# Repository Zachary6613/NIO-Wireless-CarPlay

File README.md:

# NIO Wireless CarPlay

在蔚来车机浏览器中使用的**无线 CarPlay** 方案。树莓派运行车载主机软件
[LIVI](https://github.com/f-io/LIVI)，负责 CarPlay 会话、MFi 认证、蓝牙、Wi-Fi 热点和音视频；
车机无需安装任何 App，只用浏览器打开树莓派提供的网页，即可看到 CarPlay 画面并进行触控操作。

## 工作原理

```text
iPhone
  │  蓝牙：发现、配对、Wi-Fi 切换
  │  Wi-Fi：CarPlay 会话、音视频与控制
  ▼
Raspberry Pi 4/5  +  LIVI
  │  I2C：MFi 证书 / 签名（MFI343S00177 小板）
  │
  │  车内局域网（以太网或第二张 Wi-Fi 网卡）
  ▼
蔚来车机浏览器：网页画面 + 触摸输入（https://<树莓派IP>:8080）
```

- CarPlay 协议与 MFi 认证由 Rust 编写的 **livi-helperd** 守护进程完成
- 画面经局域网推送；HTTP 浏览器使用 MSE 播放 H.264，配置 HTTPS 的浏览器使用 **WebCodecs** 解码并绘制到 canvas
- GStreamer 运行时已随仓库一起提供（linux-x64 / linux-arm64 / macos-arm64），无需自行安装

## 硬件需求

| 项目 | 说明 |
|---|---|
| 树莓派 | 4B 或 5（Pi 3 及更早不满足 OpenGL ES 3.x 要求） |
| 系统 | 64-bit Raspberry Pi OS（Debian 13 Trixie），需桌面环境 |
| MFi 小板 | 本项目 `hardware/` 中的 MFI343S00177 MiniHat，I2C-1，3.3V 常供电 |
| Wi-Fi | 一张独立 5GHz 适配器，作为 CarPlay 热点（勿与车机访问链路混用同一网卡） |
| 蓝牙 | 可先用板载蓝牙验证 |
| 供电 | 稳定的 USB-C 5V 电源 |

> MFi 芯片不是通用空白器件，需要来源合规、已写入有效证书的芯片。本仓库**不包含**任何证书、
> 私钥或认证绕过功能，使用时须遵守 Apple MFi 许可条款。

---

## 从下载到运行（完整步骤）

### 1. 启用 I2C

在树莓派上执行并重启：

```bash
sudo raspi-config nonint do_i2c 0
sudo reboot
```

确认 I2C 总线（标准 40Pin 通常是 bus 1）：

```bash
i2cdetect -l
```

### 2. 下载仓库

```bash
cd ~
git clone https://github.com/Zachary6613/NIO-Wireless-CarPlay.git
cd NIO-Wireless-CarPlay
```

仓库为私有，请确保本机已登录 GitHub（`gh auth login`）或配置好 HTTPS 凭证。

### 3. 安装系统依赖

本仓库自带安装脚本，无需从上游下载。它会安装运行所需的系统依赖（蓝牙、hostapd、
dnsmasq、avahi、pulseaudio、libva 等）以及编译和打包 AppImage 所需的主机工具
（gcc/make 工具链、patchelf、libfuse2、压缩库），但不会下载预编译 AppImage，也不会
改动 I2C 配置：

```bash
./scripts/setup-system.sh
```

> 首次执行 `pnpm run build:linux:arm64` 时，electron-builder 还会自动下载它自己的
> AppImage 工具集（mksquashfs + 静态 runtime），需联网一次；也可用环境变量
> `APPIMAGE_TOOLS_PATH` 指定预先下载好的工具集目录。

脚本结束时会检查 Node.js、pnpm、Rust 工具链。若提示缺失，按以下方式安装：

```bash
# Node.js + pnpm（Raspberry Pi OS / Debian 13 源中的 Node 为 20）
sudo apt-get install -y nodejs npm
sudo corepack enable

# Rust 工具链（编译 livi-helperd 和原生模块）
curl --proto '=https' --tlsv1.2 -sSf https://sh.rustup.rs | sh -s -- -y
. "$HOME/.cargo/env"
```

确认版本：

```bash
node -v        # v20 / v22 / v24
pnpm -v        # 本仓库锁定 pnpm 12.4.1
cargo --version
```

> 注意：不要运行 `software/LIVI/scripts/install/install.sh`。那是上游"预编译 AppImage
> 安装器"，会下载上游 AppImage、创建自启项，并按上游硬件把 MFi 配为软件 I2C bus 2 /
> GPIO 21，与本项目的硬件 I2C-1 / 常供电方案冲突。

### 4. 安装依赖

```bash
cd software/LIVI
pnpm install
```

安装结束后会自动重建原生模块并编译 livi-crypto。

### 5. 编译 helperd 守护进程

CarPlay 连接依赖 livi-helperd：

```bash
pnpm run build:helperd
```

产物位于 `native/livi-helperd/target/release/livi-helperd`。启动脚本会自动找到它；
应用正常运行后也可能把它复制到 `~/.config/LIVI/driver/` 下。

> helperd 通过 `sudo -n -E` 以 root 身份运行（需要访问硬件、管理网络）。请确认当前用户
> 具备免密 sudo，或按需配置 `/etc/sudoers`。

### 6.（可选）生成网页桥接的 HTTPS 证书

WebCodecs 需要安全上下文（HTTPS）。启动脚本检测到下列证书后会默认启用 HTTPS；无证书时才回退到 HTTP/MSE。可生成自签名证书：

```bash
mkdir -p ~/.config/LIVI/web-bridge
openssl req -x509 -newkey rsa:2048 -nodes -days 3650 \
  -keyout ~/.config/LIVI/web-bridge/key.pem \
  -out ~/.config/LIVI/web-bridge/cert.pem \
  -subj "/CN=LIVI CarPlay Bridge" \
  -addext "subjectAltName=IP:$(hostname -I | awk '{print $1}'),DNS:localhost"
```

### 7. 启动

回到项目根目录，一键启动（自动配置显示、GStreamer、helperd、kiosk 和 HTTPS 网页桥接）：

```bash
cd ~/NIO-Wireless-CarPlay
./software/LIVI/run-livi-dev.sh
```

可用的覆盖方式：

```bash
LIVI_KIOSK=0 ./software/LIVI/run-livi-dev.sh          # 临时退出全屏 kiosk
LIVI_WEB_PORT=9000 ./software/LIVI/run-livi-dev.sh    # 更改网页端口
LIVI_WEB_TLS_CERT="$HOME/.config/LIVI/web-bridge/cert.pem" \
LIVI_WEB_TLS_KEY="$HOME/.config/LIVI/web-bridge/key.pem" \
  ./software/LIVI/run-livi-dev.sh                      # 可选：启用 HTTPS + WebCodecs
```

### 8. 首次配置与访问

1. 在 LIVI 设置界面中配置 MFi（也可参考 [software/config.example.json](software/config.example.json)）：
   - `carPlayMfiI2cBus`：`1`（以 `i2cdetect -l` 实测为准）
   - `carPlayMfiPowerGpio`：`-1`（Rev A 小板常供电）
2. 在设置中选择蓝牙适配器、Wi-Fi 网卡并配置热点的国家/频段/信道
3. iPhone 通过蓝牙配对后，CarPlay 会自动切换到 Wi-Fi 连接
4. 已配置上述证书时，车机浏览器打开（自签名证书会有警告，选择“高级 → 继续前往”）：

```text
https://<树莓派IP>:8080
```

可先在树莓派本地显示器跑通整条 CarPlay 链路，再进行车机浏览器联调。

---

## 打包部署

打包成无需 Node 环境即可运行的 AppImage（产物在 `dist/`）：

```bash
cd software/LIVI
pnpm run build:linux:arm64     # 树莓派；x86 设备使用 pnpm run build:linux:x64
```

## 验证 MFi 小板

停止 LIVI 后执行（认证过程中不要反复扫描 I2C 总线）：

```bash
./scripts/check-mfi.sh 1
```

芯片应答地址应为 `0x10`。此脚本只能确认 I2C 通信，不能验证 MFi 证书是否有效。

## 树莓派运行与车机 Wi-Fi 配置

在 `software/LIVI` 目录启动、停止或查看开机自启服务：

```bash
./run-livi-dev.sh
./stop-livi-dev.sh
sudo systemctl restart livi-dev
systemctl status livi-dev --no-pager
journalctl -u livi-dev -b -f
```

不要使用 `sudo ./run-livi-dev.sh`。以 root 身份运行会切换 HOME 和 Corepack 缓存，可能导致
pnpm 再次下载。脚本内部需要的特权操作已单独授权。

使用共享的车机 Wi-Fi 运行无线 CarPlay 时，在 Web 设置页填写网络模式 `client`、车机 Wi-Fi
名称和密码、网卡 `wlan0`，并启用无线 CarPlay。保存后 LIVI 会更新 `LIVI-car-wifi`
NetworkManager 连接并自动重试。

密码必须作为系统连接持久保存（`802-11-wireless-security.psk-flags=0`），这样无人登录桌面的
冷启动也不依赖图形密码代理。修改账号或密码后可以直接冷重启验证：

```bash
sudo reboot
# 重启后
systemctl status livi-dev --no-pager
journalctl -u livi-dev -b --no-pager | \
  grep -E 'wifiClient|connected|retrying|no-secrets|Insufficient'
```

正常日志包含 `[wifiClient] connected to ...`。若出现 `no-secrets` 或
`Insufficient privileges`，执行：

```bash
nmcli -s -g 802-11-wireless-security.psk-flags connection show LIVI-car-wifi
nmcli general permissions | grep -E 'network-control|settings.modify|wifi.scan'
```

第一条应输出 `0`，NetworkManager 的相关权限应显示“是”。同时检查
`/etc/polkit-1/rules.d/49-livi-networkmanager.rules` 是否存在。

## 文档导航

| 文档 | 内容 |
|---|---|
| [docs/architecture.md](docs/architecture.md) | 系统架构、数据路径与风险边界 |
| [docs/bringup.md](docs/bringup.md) | 从空白树莓派到首轮联调 |
| [docs/development.md](docs/development.md) | LIVI 修改、构建与上游说明 |
| [software/README.md](software/README.md) | LIVI 源码结构与功能说明 |
| [hardware/README.md](hardware/README.md) | MFi 小板设计与连接表 |
| [hardware/preflight-checklist.md](hardware/preflight-checklist.md) | 投板 / 上电检查清单 |

## 常见问题

- **网页打不开 / CarPlay 连不上**：确认 8080 端口已监听（`ss -tln | grep 8080`），
  且 helperd 已编译。启动脚本找不到 helperd 会直接报错提示。
- **浏览器提示不安全**：自签名证书的正常现象，继续前往即可；车机浏览器若无法跳过警告，
  需将证书导入车机信任库。
- **只有画面没有声音**：部分浏览器限制局域网自动播放音频，需在页面内手动点"启用声音"。
- **I2C 地址不通**：以 `i2cdetect -l` 的实测总线号为准，并确认小板为 3.3V 供电。

## 许可证

LIVI 部分基于 GPL-3.0-or-later，修改和分发时请保留 [software/LIVI/LICENSE](software/LIVI/LICENSE)
与版权信息。

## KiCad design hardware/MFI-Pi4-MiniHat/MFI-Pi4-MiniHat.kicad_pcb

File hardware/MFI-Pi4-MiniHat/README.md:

# MFI Pi 4 Mini HAT - Rev A

这是树莓派 4B 前六针直插的最小 MFi Authentication 3.0 验证板。

## 接口

| J1 | Raspberry Pi 4B | 网络 |
|---:|---|---|
| 1 | 3V3 | +3V3 |
| 2 | 5V | NC |
| 3 | GPIO2/SDA1 | SDA |
| 4 | 5V | NC |
| 5 | GPIO3/SCL1 | SCL |
| 6 | GND | GND |

## U1 XDFN 顶视图

| U1 pin | 信号 | 连接 |
|---:|---|---|
| 1 | GND | GND |
| 2 | NC | 必须悬空 |
| 3 | NC | 必须悬空 |
| 4 | GND | GND |
| 5 | SDA | J1.3 + 12k pull-up |
| 6 | SCL | J1.5 + 12k pull-up |
| 7 | GND | GND |
| 8 | VCC | +3V3 |
| EP | exposed pad | GND |

## LIVI

```json
{
  "carPlayMfiI2cBus": 1,
  "carPlayMfiPowerGpio": -1
}
```

Rev A 使用常供电设计。芯片会在约 3.2-4.8 秒无活动后进入低功耗，并由发往其地址的 I2C
通信唤醒。不要把 LIVI 电源 GPIO 配为正数。

## 制造说明

- 2-layer FR-4, 1.6 mm, 1 oz copper。
- U1 XDFN 焊盘按手册推荐：0.90 x 0.30 mm，0.50 mm pitch。
- U1 中央焊盘 1.76 x 1.50 mm 接地；钢网分窗，避免漂移。
- U1 激光点/Pin 1 丝印必须与 PCB 圆点一致。
- J1 是装在 PCB 底面的 2x3 母座，板从树莓派上方插入。
- 下单前在 KiCad 中再次执行 DRC，并用所购母座的实物尺寸检查机械间隙。

## 已生成文件

- `MFI-Pi4-MiniHat.kicad_pcb`：KiCad 10 PCB 源文件。
- `BOM.csv`：首版物料表。
- `drc-errors.txt`：KiCad 10.0.6 检查报告；0 errors、0 unconnected pads。
- `fabrication/`：Gerber、Excellon 钻孔、钻孔图和 Gerber job 文件。
- `MFI-Pi4-MiniHat-Gerbers.zip`：可交给板厂的压缩包。
- `panel-2x2/`：60.1 x 44.1 mm 的 2×2 同款鼠咬孔拼板，带工艺边、定位孔、基准点、
  完整拼板 BOM/CPL 和嘉立创下单说明。优先使用其中的
  `JLCPCB-2x2-Panel-Order-Package.zip` 下单。

DRC 清零只说明设计满足当前规则，不代替封装实物核对。尤其需要向供应商确认购买的是
`MFI343S00177-L` XDFN 版本，并确认 2x3 母座从 PCB 底面装配后的方向和高度。

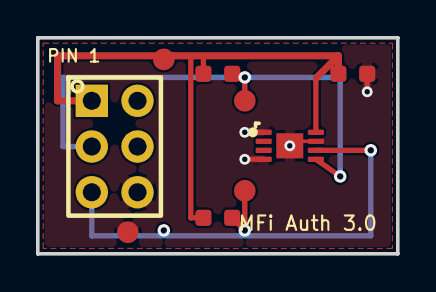
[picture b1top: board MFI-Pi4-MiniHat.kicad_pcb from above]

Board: 2 copper layers, 20.0 x 12.0 mm, 9 parts (0 on the bottom side), 4 nets.

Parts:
C1: 100nF; C_0603
J1: RPi_GPIO_1-6; RPi_2x03_Female_Bottom
R1, R2: 12k; R_0603
TP1: 3V3; TestPoint
TP2: SDA; TestPoint
TP3: SCL; TestPoint
TP4: GND; TestPoint
U1: MFI343S00177-L; MFI343S00177_XDFN8_2x3mm_P0.5

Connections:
+3V3: C1.1, J1.1, R1.1, R2.1, TP1.1, U1.8
GND: C1.2, J1.6, TP4.1, U1.1, U1.4, U1.7, U1.9
SCL: J1.5, R2.2, TP3.1, U1.6
SDA: J1.3, R1.2, TP2.1, U1.5

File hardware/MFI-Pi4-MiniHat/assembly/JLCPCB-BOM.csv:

Comment,Designator,Footprint,LCSC Part #,Manufacturer Part Number,Assembly
MFI343S00177-L,U1,XDFN-8_2x3mm_P0.5mm,C33770534,MFI343S00177-L,SMT top
100nF 50V X7R,C1,0603,C14663,CC0603KRX7R9BB104,SMT top
12k 1%,"R1,R2",0603,C114659,RC0603FR-0712KL,SMT top
2x3 female 2.54mm,J1,PinSocket_2x03_P2.54mm,,User selected,DNP - hand solder on bottom

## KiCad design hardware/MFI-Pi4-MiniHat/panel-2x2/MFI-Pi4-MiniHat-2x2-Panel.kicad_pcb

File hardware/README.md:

# MFI343S00177 Raspberry Pi 验证板

## Rev A 树莓派侧连接（已确定）

| 信号 | BCM | 40Pin 物理脚 | 小板用途 |
|---|---:|---:|---|
| 3V3 | — | 1 | MFi 芯片与 I2C 上拉电源 |
| SDA1 | GPIO2 | 3 | I2C SDA |
| SCL1 | GPIO3 | 5 | I2C SCL |
| GND | — | 6 | 地 |
Rev A 不使用 MFI_PWR_EN，芯片由 3.3 V 常供电，详见 `MFI-Pi4-MiniHat/`。

Rev A 使用 2x3 母座，仅覆盖 Pin 1-6；Pin 2/4 的 5 V 焊盘保持 NC。Pin 1、Pin 3、Pin 5、
Pin 6 均设置醒目的丝印或测试点。

## Rev A 实际电路

- U1 由 Pi Pin 1 的 3.3 V 常供电，没有 EN 或负载开关。
- SDA/SCL 各使用 12 kΩ 上拉到 3.3 V。
- U1 旁路电容为 100 nF，靠近 VCC 放置。
- TP1–TP4 分别提供 3V3、SDA、SCL、GND 测试点。
- Pi Pin 2/4 的 5 V 焊盘不连接。
- J1 为底面手焊件；其余 U1/C1/R1/R2 为顶面贴片件。

## 已由手册确认

- XDFN 2 x 3 mm、8 pin、0.5 mm pitch。
- Pin 1/4/7=GND，2/3=NC，5=SDA，6=SCL，8=VCC；EP 可接地。
- VCC 1.71-3.6 V，SCL 最大 400 kHz。
- 100 nF 旁路；SDA/SCL 上拉到同一 VCC，阻值不大于 12 kΩ。
- 8-bit 写/读地址 0x20/0x21，即 Linux 7-bit 地址 0x10。

生产文件和下单说明位于 `MFI-Pi4-MiniHat/panel-2x2/`。

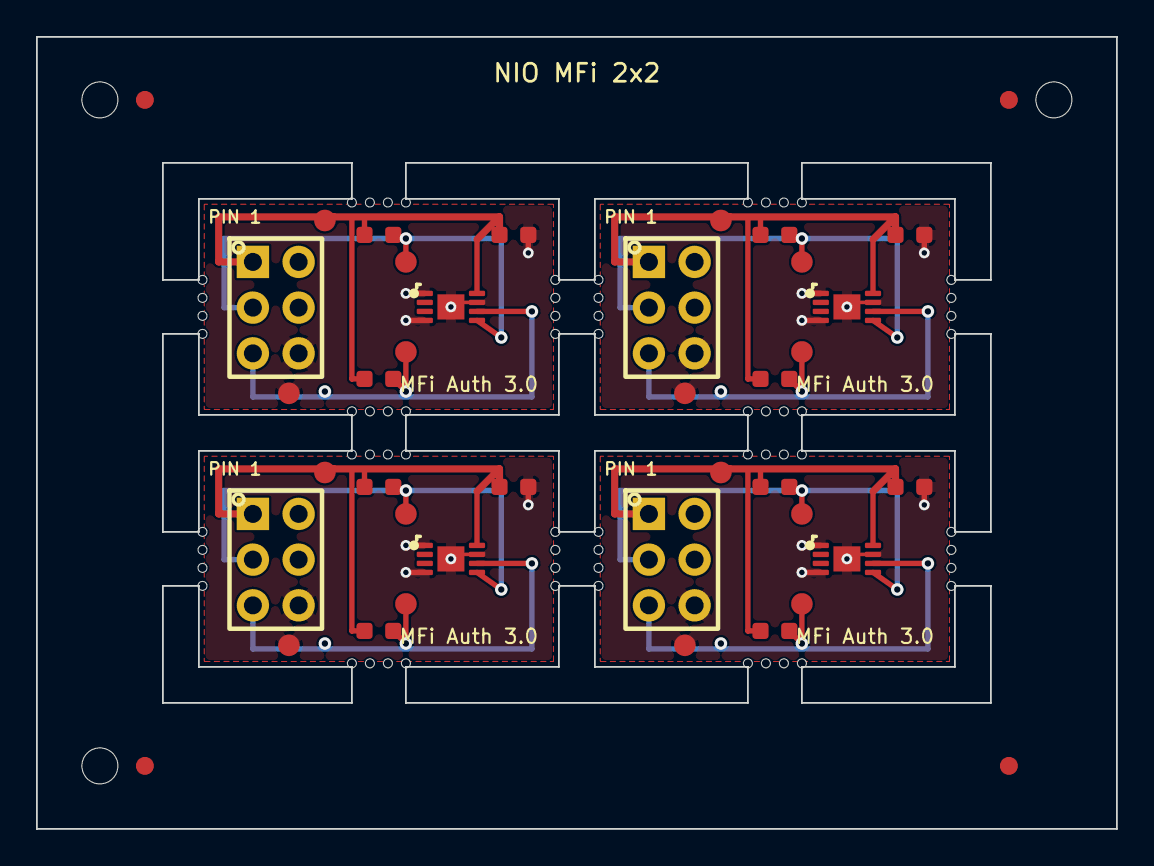
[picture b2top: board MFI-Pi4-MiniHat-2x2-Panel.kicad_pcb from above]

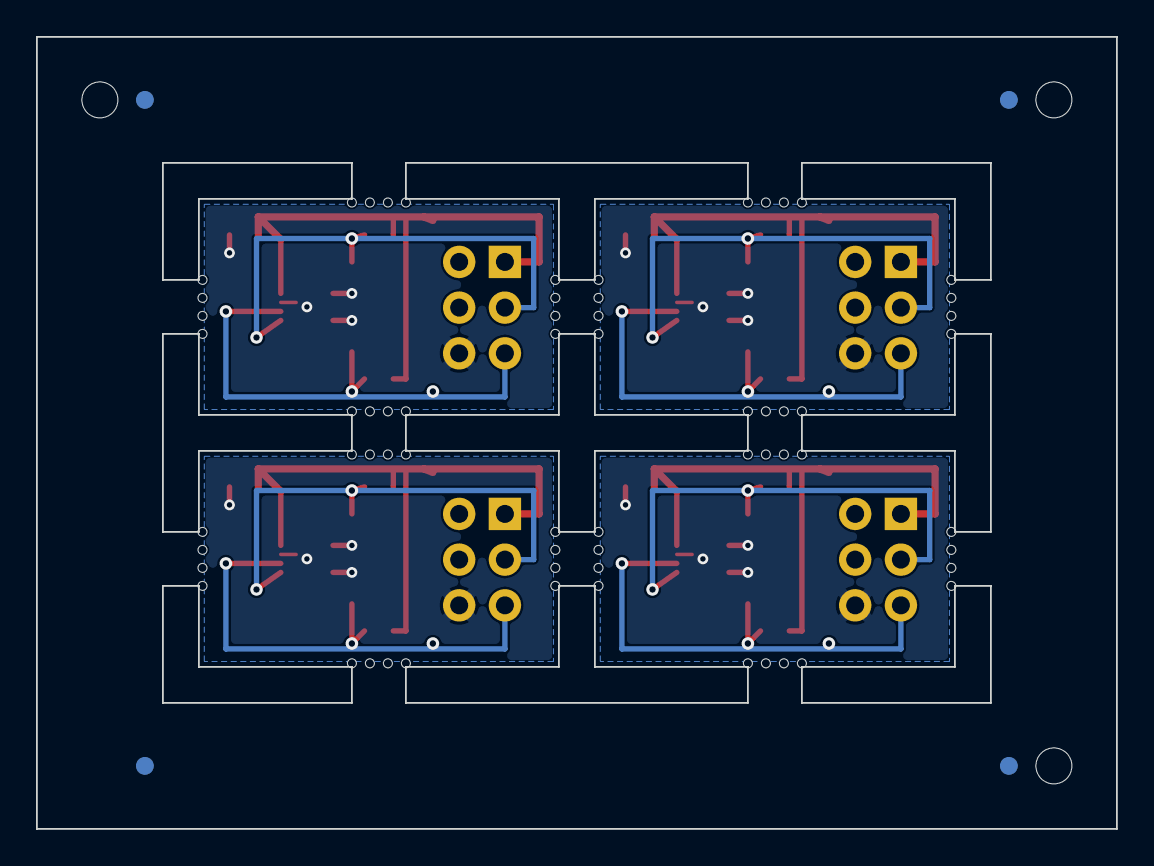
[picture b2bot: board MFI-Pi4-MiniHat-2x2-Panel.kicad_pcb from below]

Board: 2 copper layers, 60.0 x 44.0 mm, 111 parts (4 on the bottom side), 16 nets.

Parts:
B0-C1, B1-C1, B2-C1, B3-C1: 100nF; C_0603
B0-J1, B1-J1, B2-J1, B3-J1: RPi_GPIO_1-6; RPi_2x03_Female_Bottom
B0-R1, B0-R2, B1-R1, B1-R2, B2-R1, B2-R2, B3-R1, B3-R2: 12k; R_0603
B0-TP1, B1-TP1, B2-TP1, B3-TP1: 3V3; TestPoint
B0-TP2, B1-TP2, B2-TP2, B3-TP2: SDA; TestPoint
B0-TP3, B1-TP3, B2-TP3, B3-TP3: SCL; TestPoint
B0-TP4, B1-TP4, B2-TP4, B3-TP4: GND; TestPoint
B0-U1, B1-U1, B2-U1, B3-U1: MFI343S00177-L; MFI343S00177_XDFN8_2x3mm_P0.5
KiKit_FID_B_1, KiKit_FID_B_2, KiKit_FID_B_3, KiKit_FID_B_4: Fiducial
KiKit_FID_T_1, KiKit_FID_T_2, KiKit_FID_T_3, KiKit_FID_T_4: Fiducial
KiKit_MB_1_1, KiKit_MB_1_2, KiKit_MB_1_3, KiKit_MB_1_4, KiKit_MB_2_1, KiKit_MB_2_2, KiKit_MB_2_3, KiKit_MB_2_4, KiKit_MB_3_1, KiKit_MB_3_2, KiKit_MB_3_3, KiKit_MB_3_4, KiKit_MB_4_1, KiKit_MB_4_2, KiKit_MB_4_3, KiKit_MB_4_4, KiKit_MB_5_1, KiKit_MB_5_2, KiKit_MB_5_3, KiKit_MB_5_4, KiKit_MB_6_1, KiKit_MB_6_2, KiKit_MB_6_3, KiKit_MB_6_4, KiKit_MB_7_1, KiKit_MB_7_2, KiKit_MB_7_3, KiKit_MB_7_4, KiKit_MB_8_1, KiKit_MB_8_2, KiKit_MB_8_3, KiKit_MB_8_4, KiKit_MB_9_1, KiKit_MB_9_2, KiKit_MB_9_3, KiKit_MB_9_4, KiKit_MB_10_1, KiKit_MB_10_2, KiKit_MB_10_3, KiKit_MB_10_4, KiKit_MB_11_1, KiKit_MB_11_2, KiKit_MB_11_3, KiKit_MB_11_4, KiKit_MB_12_1, KiKit_MB_12_2, KiKit_MB_12_3, KiKit_MB_12_4, KiKit_MB_13_1, KiKit_MB_13_2, KiKit_MB_13_3, KiKit_MB_13_4, KiKit_MB_14_1, KiKit_MB_14_2, KiKit_MB_14_3, KiKit_MB_14_4, KiKit_MB_15_1, KiKit_MB_15_2, KiKit_MB_15_3, KiKit_MB_15_4, KiKit_MB_16_1, KiKit_MB_16_2, KiKit_MB_16_3, KiKit_MB_16_4: NPTH
KiKit_TO_1, KiKit_TO_2, KiKit_TO_3: NPTH

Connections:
Board_0-+3V3: B0-C1.1, B0-J1.1, B0-R1.1, B0-R2.1, B0-TP1.1, B0-U1.8
Board_0-GND: B0-C1.2, B0-J1.6, B0-TP4.1, B0-U1.1, B0-U1.4, B0-U1.7, B0-U1.9
Board_0-SCL: B0-J1.5, B0-R2.2, B0-TP3.1, B0-U1.6
Board_0-SDA: B0-J1.3, B0-R1.2, B0-TP2.1, B0-U1.5
Board_1-+3V3: B1-C1.1, B1-J1.1, B1-R1.1, B1-R2.1, B1-TP1.1, B1-U1.8
Board_1-GND: B1-C1.2, B1-J1.6, B1-TP4.1, B1-U1.1, B1-U1.4, B1-U1.7, B1-U1.9
Board_1-SCL: B1-J1.5, B1-R2.2, B1-TP3.1, B1-U1.6
Board_1-SDA: B1-J1.3, B1-R1.2, B1-TP2.1, B1-U1.5
Board_2-+3V3: B2-C1.1, B2-J1.1, B2-R1.1, B2-R2.1, B2-TP1.1, B2-U1.8
Board_2-GND: B2-C1.2, B2-J1.6, B2-TP4.1, B2-U1.1, B2-U1.4, B2-U1.7, B2-U1.9
Board_2-SCL: B2-J1.5, B2-R2.2, B2-TP3.1, B2-U1.6
Board_2-SDA: B2-J1.3, B2-R1.2, B2-TP2.1, B2-U1.5
Board_3-+3V3: B3-C1.1, B3-J1.1, B3-R1.1, B3-R2.1, B3-TP1.1, B3-U1.8
Board_3-GND: B3-C1.2, B3-J1.6, B3-TP4.1, B3-U1.1, B3-U1.4, B3-U1.7, B3-U1.9
Board_3-SCL: B3-J1.5, B3-R2.2, B3-TP3.1, B3-U1.6
Board_3-SDA: B3-J1.3, B3-R1.2, B3-TP2.1, B3-U1.5
